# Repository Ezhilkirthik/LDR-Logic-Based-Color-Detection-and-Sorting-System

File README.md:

# LDR-Logic-Based-Color-Detection-and-Sorting-System
LDR Logic-Based Color Detection and Sorting System. Microcontroller-free automation using Analog &amp; Digital Electronics. 8-color detection (RGB, CMYK, White/Black) sorted by a servo motor controlled by Op-Amps, a Decoder, and 555 Timers (PWM). Low-cost, purely hardware solution.

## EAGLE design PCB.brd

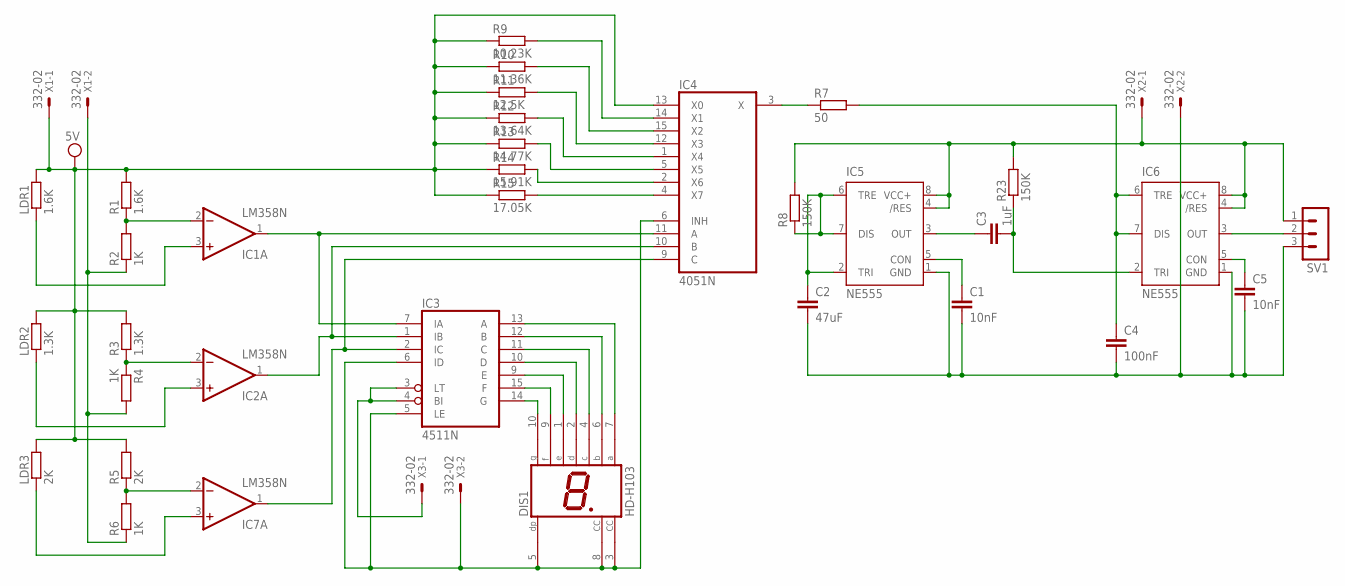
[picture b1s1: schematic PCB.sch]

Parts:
C1, C5: 10nF; C2.5-2
C2: 47uF; C2.5-2
C3: 1uF; C2.5-2
C4: 100nF; C2.5-2
DIS1: HD-H103; HDSP-M
IC1, IC2, IC7: LM358N; DIL08
IC3: 4511N; DIL16
IC4: 4051N; DIL16
IC5, IC6: NE555; DIL-08
LDR1: 1.6K; 0207/10
LDR2: 1.3K; 0207/10
LDR3: 2K; 0207/10
R1: 1.6K; 0207/10
R2, R4, R6: 1K; 0207/10
R3: 1.3K; 0207/10
R5: 2K; 0207/10
R7: 50; 0207/10
R8, R23: 150K; 0207/10
R9: 10.23K; 0207/10
R10: 11.36K; 0207/10
R11: 12.5K; 0207/10
R12: 13.64K; 0207/10
R13: 14.77K; 0207/10
R14: 15.91K; 0207/10
R15: 17.05K; 0207/10
SV1: MA03-1
X1, X2, X3: 332-02

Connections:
GND: IC4.8 (GND)
unnamed: IC1.2 (-IN), R1.1, R2.2
unnamed: IC2.2 (-IN), R3.1, R4.1
unnamed: IC7.2 (-IN), R5.1, R6.2
unnamed: DIS1.10 (G), IC3.14 (G)
unnamed: DIS1.9 (F), IC3.15 (F)
unnamed: IC1.3 (+IN), LDR1.1
unnamed: IC2.3 (+IN), LDR2.1
unnamed: IC7.3 (+IN), LDR3.1
unnamed: IC1.1 (OUT), IC3.7 (IA), IC4.11 (A)
unnamed: IC2.1 (OUT), IC3.1 (IB), IC4.10 (B)
unnamed: IC3.2 (IC), IC4.9 (C), IC7.1 (OUT)
unnamed: IC4.4 (X7), R15.2
unnamed: DIS1.1 (E), IC3.9 (E)
unnamed: DIS1.2 (D), IC3.10 (D)
unnamed: DIS1.4 (C), IC3.11 (C)
unnamed: DIS1.6 (B), IC3.12 (B)
unnamed: DIS1.7 (A), IC3.13 (A)
unnamed: DIS1.3 (CC), DIS1.5 (DP), DIS1.8 (CC), IC3.5 (LE), IC3.6 (ID), IC4.6 (INH), X3.2
unnamed: IC4.2 (X6), R14.2
unnamed: IC4.5 (X5), R13.2
unnamed: IC4.1 (X4), R12.2
unnamed: IC4.12 (X3), R11.2
unnamed: IC4.15 (X2), R10.2
unnamed: IC4.14 (X1), R9.2
unnamed: IC4.3 (X), R7.1
unnamed: C1.1, IC5.5 (CON)
unnamed: C3.1, IC5.3 (OUT)
unnamed: C3.2, IC6.2 (TRI), R23.1
unnamed: C2.1, IC5.2 (TRI), IC5.6 (TRE), IC5.7 (DIS), R8.1
unnamed: C4.1, IC6.6 (TRE), IC6.7 (DIS), R7.2
unnamed: C5.1, IC6.5 (CON)
unnamed: IC6.3 (OUT), SV1.2
unnamed: C1.2, C2.2, C4.2, C5.2, IC5.1 (GND), IC6.1 (GND), SV1.3, X2.2
unnamed: IC3.3 (LT), IC3.4 (BI), X3.1
unnamed: R2.1, R4.2, R6.1, X1.2
unnamed: IC5.4 (/RES), IC5.8 (VCC+), IC6.4 (/RES), IC6.8 (VCC+), R8.2, R23.2, SV1.1, X2.1
V+: IC1.8 (V+), IC2.8 (V+), IC7.8 (V+)
V-: IC1.4 (V-), IC2.4 (V-), IC7.4 (V-)
VCC: IC4.13 (X0), IC4.16 (VCC), LDR1.2, LDR2.2, LDR3.2, R1.2, R3.2, R5.2, R9.1, R10.1, R11.1, R12.1, R13.1, R14.1, R15.1, X1.1
VDD: IC3.16 (VDD)
VEE: IC4.7 (VEE)
VSS: IC3.8 (VSS)

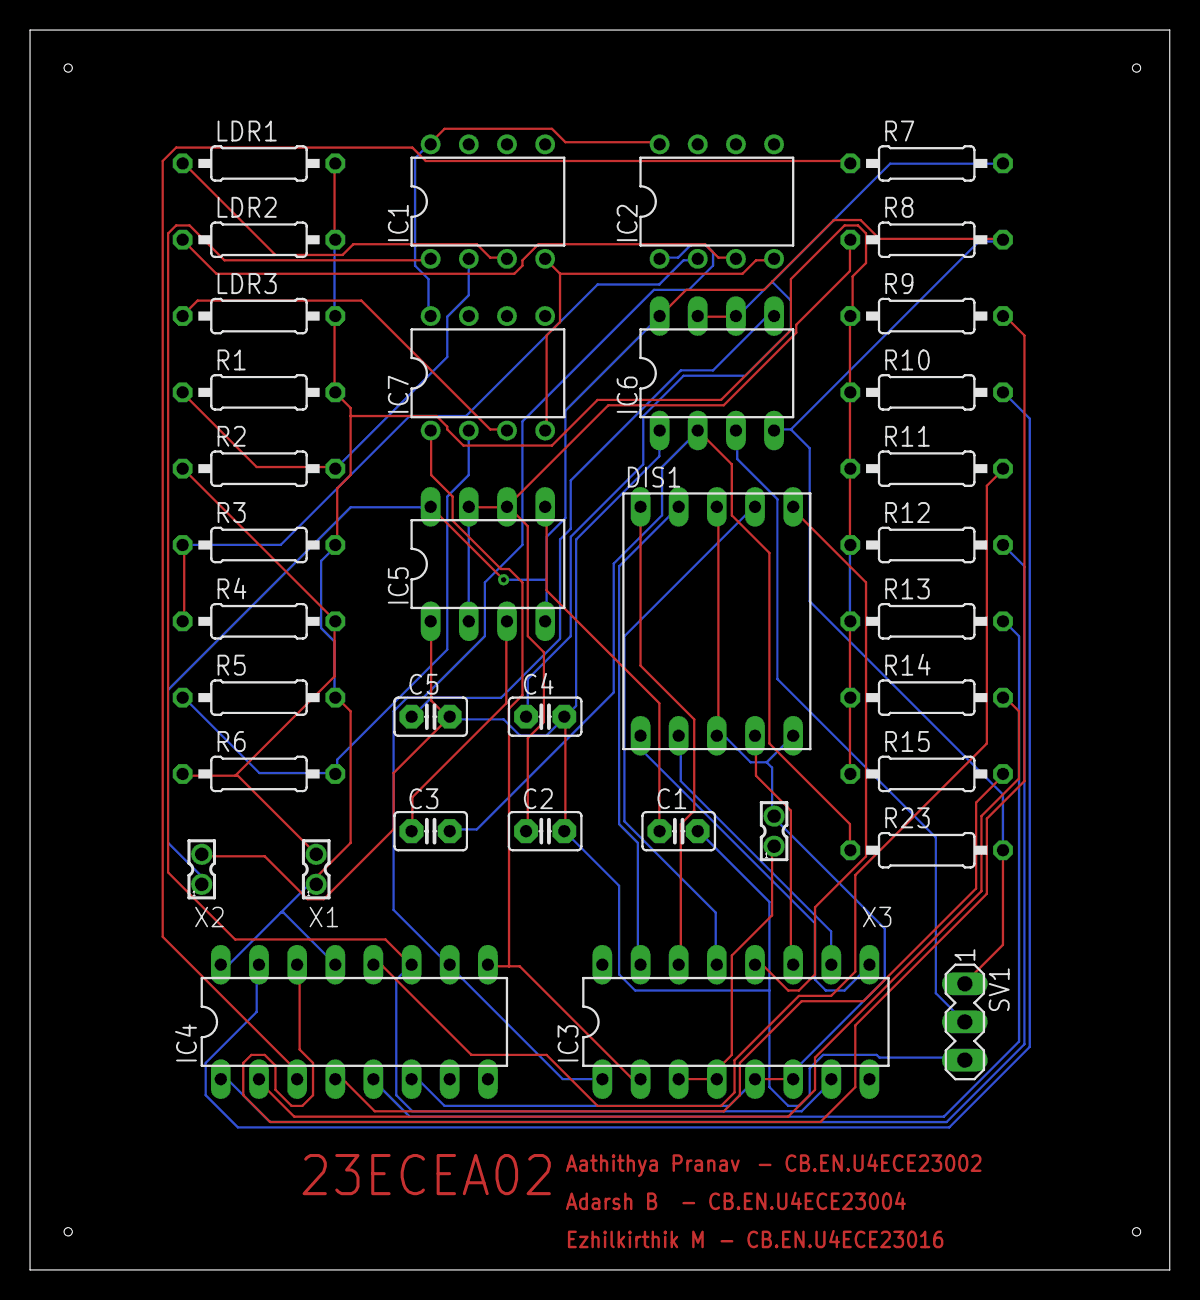
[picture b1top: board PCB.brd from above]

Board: 2 copper layers, 75.9 x 82.5 mm, 36 parts (0 on the bottom side), 39 nets.

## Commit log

2025-11-24 Create a
